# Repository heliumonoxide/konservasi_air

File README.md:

# Water Quality Monitoring Device

## Introduction
This project is **a Water Quality Monitoring System** supported by both a web interface and an OLED display. The device utilizes the SPIFFS (SPI Flash File System) feature of the ESP32 microcontroller to deploy a native web application (HTML, CSS, JavaScript) over a wide-area local network. The system directly links the web interface to real-time data received by the ESP32, providing users with seamless access to water quality metrics. 
 
### Concerns
The Drinking Fountain is essential for students at the Faculty of Engineering, Universitas Indonesia, providing water and reducing plastic use. However, concerns about water quality have led 60% of students to still purchase bottled water. A survey revealed that 90% of respondents believe the water quality in certain buildings is poor, particularly due to its taste. Addressing these concerns is crucial to encouraging students to trust and use the water fountains.

### Usage
1. The device measures all test parameters on drinking water samples.
2. It displays results in a human-readable format via an OLED screen.
3. The device sends water test data to a designed webpage.
4. Its microcontroller deploys a server-based webpage accessible to anyone on the UI Wi-Fi, providing water fountain quality information.

## PCB Design
PCB made using Altium and printed using PCB printing machine.
\

> Here are the made PCB picture
> \
> 
## Hardware Design

## Requirements Software
For installation, within Arduino IDE, the following libraries needs to be installed under Sketch -> Include Library -> Manage Libraries:
* ArduinoJson by Benoit Blanchon
* WebSockets by Markus Sattler
* WiFi 

The following to libraries need to be downloaded, unpacked and copied to the "Arduino" folder (Required for ESPAsyncWebServer)
- https://github.com/me-no-dev/ESPAsyncWebServerWater
- https://github.com/me-no-dev/AsyncTCP

Required to make SPIFFS.h work:
https://github.com/me-no-dev/arduino-esp32fs-plugin/releases/

### How to Install Packages Manually
- Click on the link provided in each package
- Download zip file of the packages through the 'code' dropdown
- Unzip/extract the downloaded file
- Put the packages folder in to libraries folder in Arduino Folder (usually in C:/Users/Documents/Arduino)

### How to Install Tools Manually
- Click on the link provided in each package
- Download zip file of the tools in the asset section of the page
- Unzip/extract the downloaded file
- Put the asset folder into tools folder in Arduino Folder (usually in C:/Users/Documents/Arduino)
- After putting asset folder into tools folder, restart the Arduino IDE
- Check if in the dropdown section of Tools there is ESP32 Sketch Data Upload
- [X] if there is, then you are set to go

## Code Pre-configuration
In the ino. files in this section,
```
// SSID and password of Wifi connection:
const char* ssid = "[Your Wifi Name]";
const char* password = "[Your Wifi Password]";
```
ssid and password need to be changed according to the router/wifi that is used.

> Before uploading the code, **please upload data sketch first using ESP32 Sketch Data Upload button on tools dropdown section**

## Hardware Requirement
Before making the actual device, there are some items that you need to have:
- Analog pH Sensor kit by DFRobot
- OleD White 0.96 inch I2C IIC 128x64 display module lcd
- Oled Display 0.91 inch 128x32 LCD Screen
- Micro DC step down 4v-24v to 3.3v 5v 3A Buck super mini
- ESP32
- KY-023 Analog Dual Axis XY Joystick
- Calibration Buffer Powder/liquid
- PH Meter Sensor board ph4502C for Arduino
- Robotdyn e 3.3v/5v logic 4A/16A 600V for Arduino - 4A
- PTC Thermostat
- Heatsink
- Hi-Link HLK-5M05
- Modul 16bit I2C ADS1115
- Jumper set
- NTC Thermistor
- TDS Sensor
- Turbidity Sensor
- Servo

> Before using all the sensor, please configurate and calibrate first.
## Created by
Bryan Indarto, Aldy Raja, Theonaldo, dan Reza Febrian

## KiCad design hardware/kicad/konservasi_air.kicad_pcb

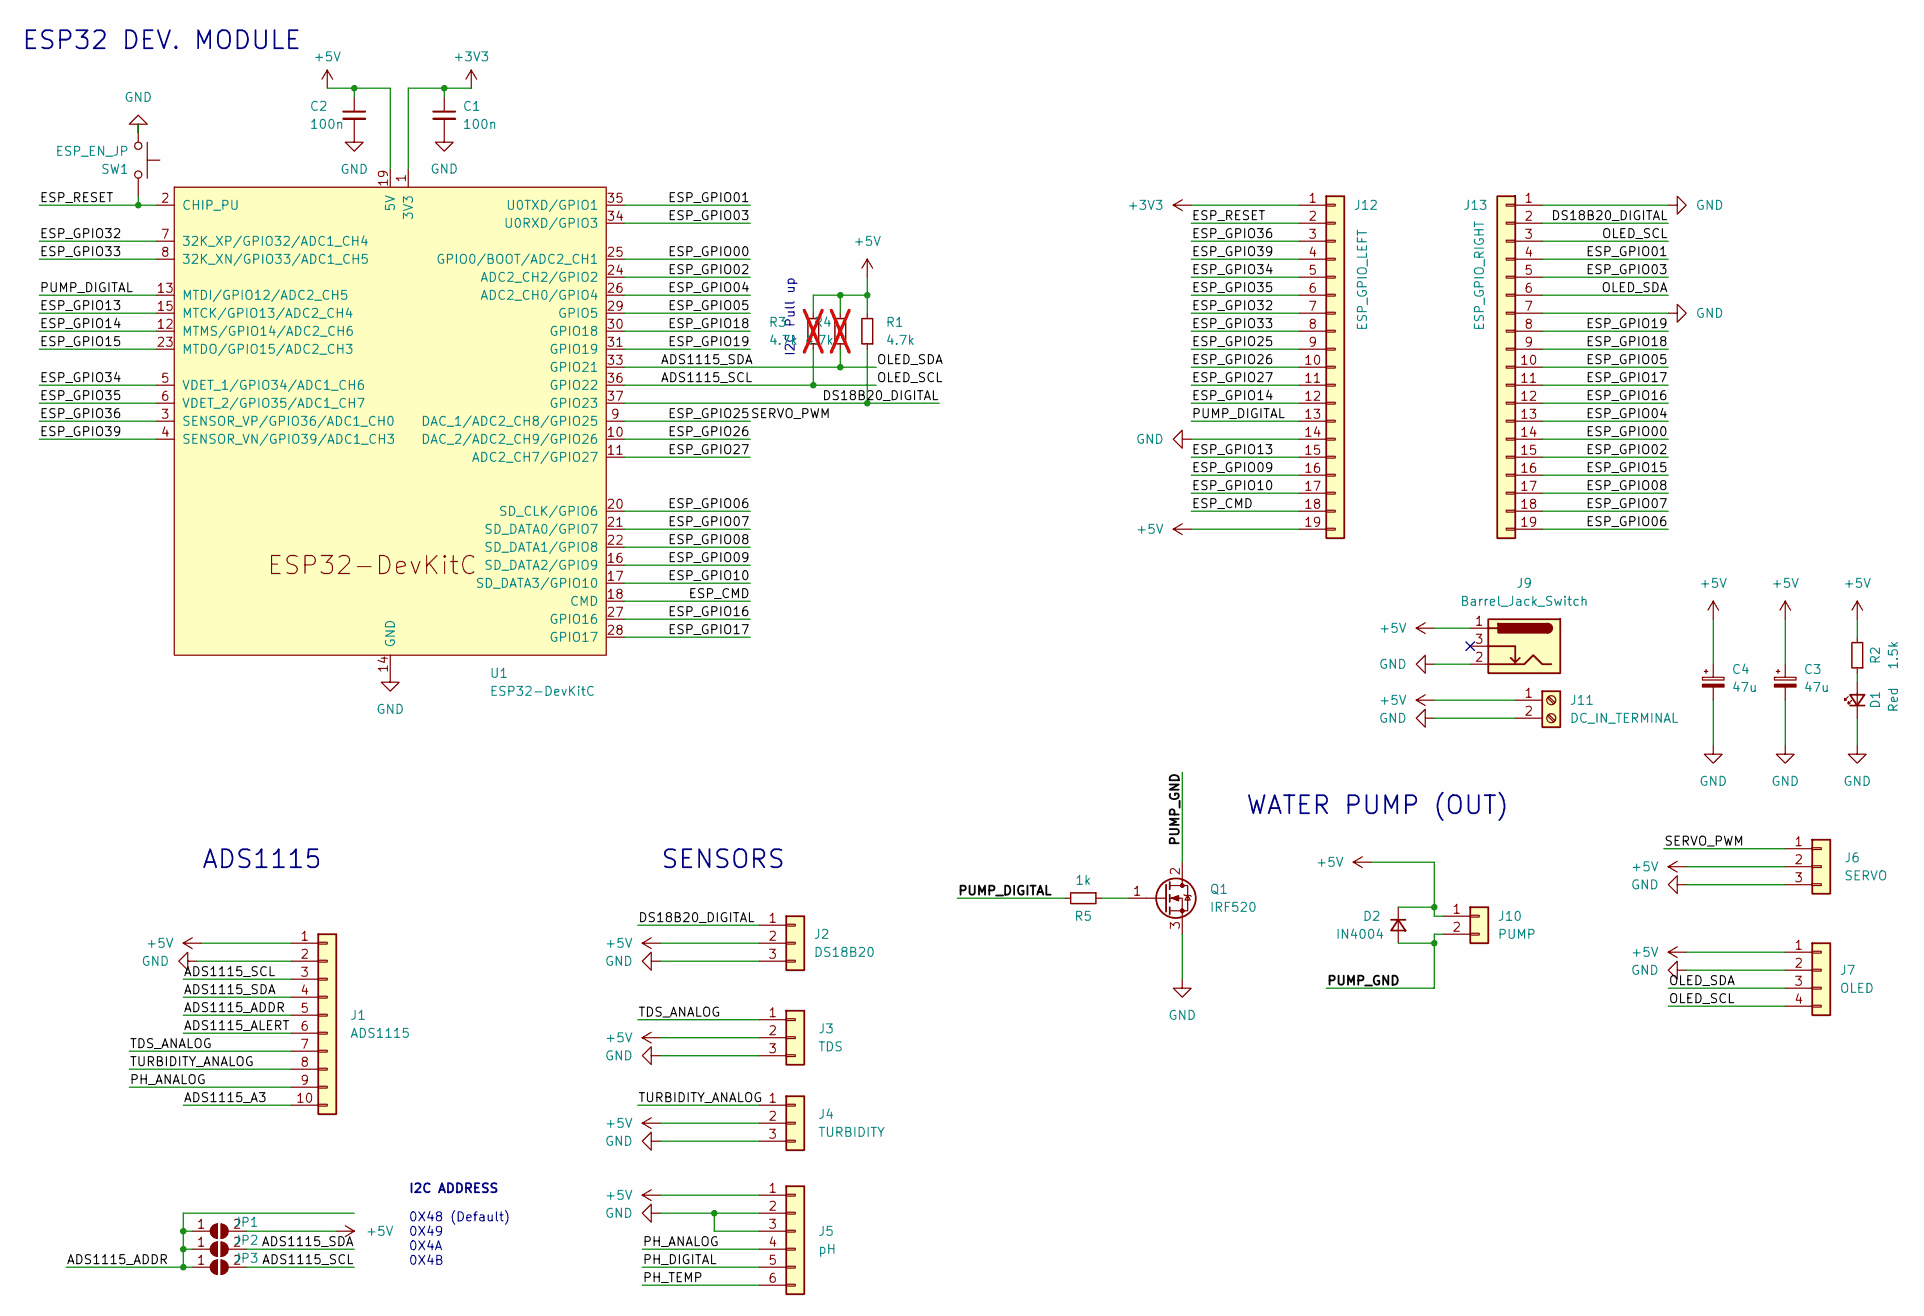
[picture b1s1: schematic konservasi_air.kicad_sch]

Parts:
C1, C2: 100n; C_Disc_D5.0mm_W2.5mm_P5.00mm
C3, C4: 47u; C_Radial_D5.0mm_H11.0mm_P2.00mm
D1: Red; LED_D3.0mm
D2: IN4004; D_DO-34_SOD68_P7.62mm_Horizontal
J1: ADS1115; PinSocket_1x10_P2.54mm_Vertical
J2: DS18B20; Molex_SL_171971-0003_1x03_P2.54mm_Vertical
J3: TDS; Molex_SL_171971-0003_1x03_P2.54mm_Vertical
J4: TURBIDITY; Molex_SL_171971-0003_1x03_P2.54mm_Vertical
J5: pH; Molex_SL_171971-0006_1x06_P2.54mm_Vertical
J6: SERVO; Molex_SL_171971-0003_1x03_P2.54mm_Vertical
J7: OLED; Molex_SL_171971-0004_1x04_P2.54mm_Vertical
J9: Barrel_Jack_Switch; BarrelJack_Horizontal
J10: PUMP; Molex_SL_171971-0002_1x02_P2.54mm_Vertical
J11: DC_IN_TERMINAL; TerminalBlock_Phoenix_MPT-0,5-2-2.54_1x02_P2.54mm_Horizontal
J12: ESP_GPIO_LEFT; PinHeader_1x19_P2.54mm_Vertical
J13: ESP_GPIO_RIGHT; PinHeader_1x19_P2.54mm_Vertical
JP1: ADS1115_ADDR_5V; SolderJumper-2_P1.3mm_Open_RoundedPad1.0x1.5mm
JP2: ADS1115_ADDR_SDA; SolderJumper-2_P1.3mm_Open_RoundedPad1.0x1.5mm
JP3: ADS1115_ADDR_SCL; SolderJumper-2_P1.3mm_Open_RoundedPad1.0x1.5mm
Q1: IRF520; TO-220-3_Vertical
R1: 4.7k; R_Axial_DIN0204_L3.6mm_D1.6mm_P7.62mm_Horizontal
R2: 1.5k; R_Axial_DIN0204_L3.6mm_D1.6mm_P7.62mm_Horizontal
R3, R4: 4.7k; R_Axial_DIN0204_L3.6mm_D1.6mm_P7.62mm_Horizontal; not fitted
R5: 1k; R_Axial_DIN0204_L3.6mm_D1.6mm_P7.62mm_Horizontal
SW1: ESP_EN_JP; Molex_SL_171971-0002_1x02_P2.54mm_Vertical
U1: ESP32-DevKitC

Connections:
+3V3: C1.1, J12.1, U1.1 (3V3)
+5V: C2.1, C3.1, C4.1, D2.1 (K), J1.1, J2.2, J3.2, J4.2, J5.1, J6.2, J7.1, J9.1, J10.1, J11.1, J12.19, JP1.2 (B), R1.2, R2.2, R3.2, R4.2, U1.19 (5V)
/ADS1115_A3: J1.10
/ADS1115_ADDR: J1.5, JP1.1 (A), JP2.1 (A), JP3.1 (A)
/ADS1115_ALERT: J1.6
/ADS1115_SCL: J1.3, J7.4, J13.3, JP3.2 (B), R3.1, U1.36 (GPIO22)
/ADS1115_SDA: J1.4, J7.3, J13.6, JP2.2 (B), R4.1, U1.33 (GPIO21)
/DS18B20_DIGITAL: J2.1, J13.2, R1.1, U1.37 (GPIO23)
/ESP_CMD: J12.18, U1.18 (CMD)
/ESP_GPIO00: J13.14, U1.25 (GPIO0/BOOT/ADC2_CH1)
/ESP_GPIO01: J13.4, U1.35 (U0TXD/GPIO1)
/ESP_GPIO02: J13.15, U1.24 (ADC2_CH2/GPIO2)
/ESP_GPIO03: J13.5, U1.34 (U0RXD/GPIO3)
/ESP_GPIO04: J13.13, U1.26 (ADC2_CH0/GPIO4)
/ESP_GPIO05: J13.10, U1.29 (GPIO5)
/ESP_GPIO06: J13.19, U1.20 (SD_CLK/GPIO6)
/ESP_GPIO07: J13.18, U1.21 (SD_DATA0/GPIO7)
/ESP_GPIO08: J13.17, U1.22 (SD_DATA1/GPIO8)
/ESP_GPIO09: J12.16, U1.16 (SD_DATA2/GPIO9)
/ESP_GPIO10: J12.17, U1.17 (SD_DATA3/GPIO10)
/ESP_GPIO13: J12.15, U1.15 (MTCK/GPIO13/ADC2_CH4)
/ESP_GPIO14: J12.12, U1.12 (MTMS/GPIO14/ADC2_CH6)
/ESP_GPIO15: J13.16, U1.23 (MTDO/GPIO15/ADC2_CH3)
/ESP_GPIO16: J13.12, U1.27 (GPIO16)
/ESP_GPIO17: J13.11, U1.28 (GPIO17)
/ESP_GPIO18: J13.9, U1.30 (GPIO18)
/ESP_GPIO19: J13.8, U1.31 (GPIO19)
/ESP_GPIO25: J6.1, J12.9, U1.9 (DAC_1/ADC2_CH8/GPIO25)
/ESP_GPIO26: J12.10, U1.10 (DAC_2/ADC2_CH9/GPIO26)
/ESP_GPIO27: J12.11, U1.11 (ADC2_CH7/GPIO27)
/ESP_GPIO32: J12.7, U1.7 (32K_XP/GPIO32/ADC1_CH4)
/ESP_GPIO33: J12.8, U1.8 (32K_XN/GPIO33/ADC1_CH5)
/ESP_GPIO34: J12.5, U1.5 (VDET_1/GPIO34/ADC1_CH6)
/ESP_GPIO35: J12.6, U1.6 (VDET_2/GPIO35/ADC1_CH7)
/ESP_GPIO36: J12.3, U1.3 (SENSOR_VP/GPIO36/ADC1_CH0)
/ESP_GPIO39: J12.4, U1.4 (SENSOR_VN/GPIO39/ADC1_CH3)
/ESP_RESET: J12.2, SW1.2, U1.2 (CHIP_PU)
/PH_ANALOG: J1.9, J5.4
/PH_DIGITAL: J5.5
/PH_TEMP: J5.6
/PUMP_DIGITAL: J12.13, R5.2, U1.13 (MTDI/GPIO12/ADC2_CH5)
/PUMP_GND: D2.2 (A), J10.2, Q1.2 (D)
/TDS_ANALOG: J1.7, J3.1
/TURBIDITY_ANALOG: J1.8, J4.1
GND: C1.2, C2.2, C3.2, C4.2, D1.1 (K), J1.2, J2.3, J3.3, J4.3, J5.2, J5.3, J6.3, J7.2, J9.2, J11.2, J12.14, J13.1, J13.7, Q1.3 (S), SW1.1, U1.14 (GND), U1.32 (GND), U1.38 (GND)
unnamed: D1.2 (A), R2.1
unnamed: Q1.1 (G), R5.1

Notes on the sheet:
ESP32 DEV. MODULE
ADS1115
I2C Pull up
WATER PUMP (OUT)
I2C ADDRESS
0X48 (Default) 0X49 0X4A 0X4B
SENSORS

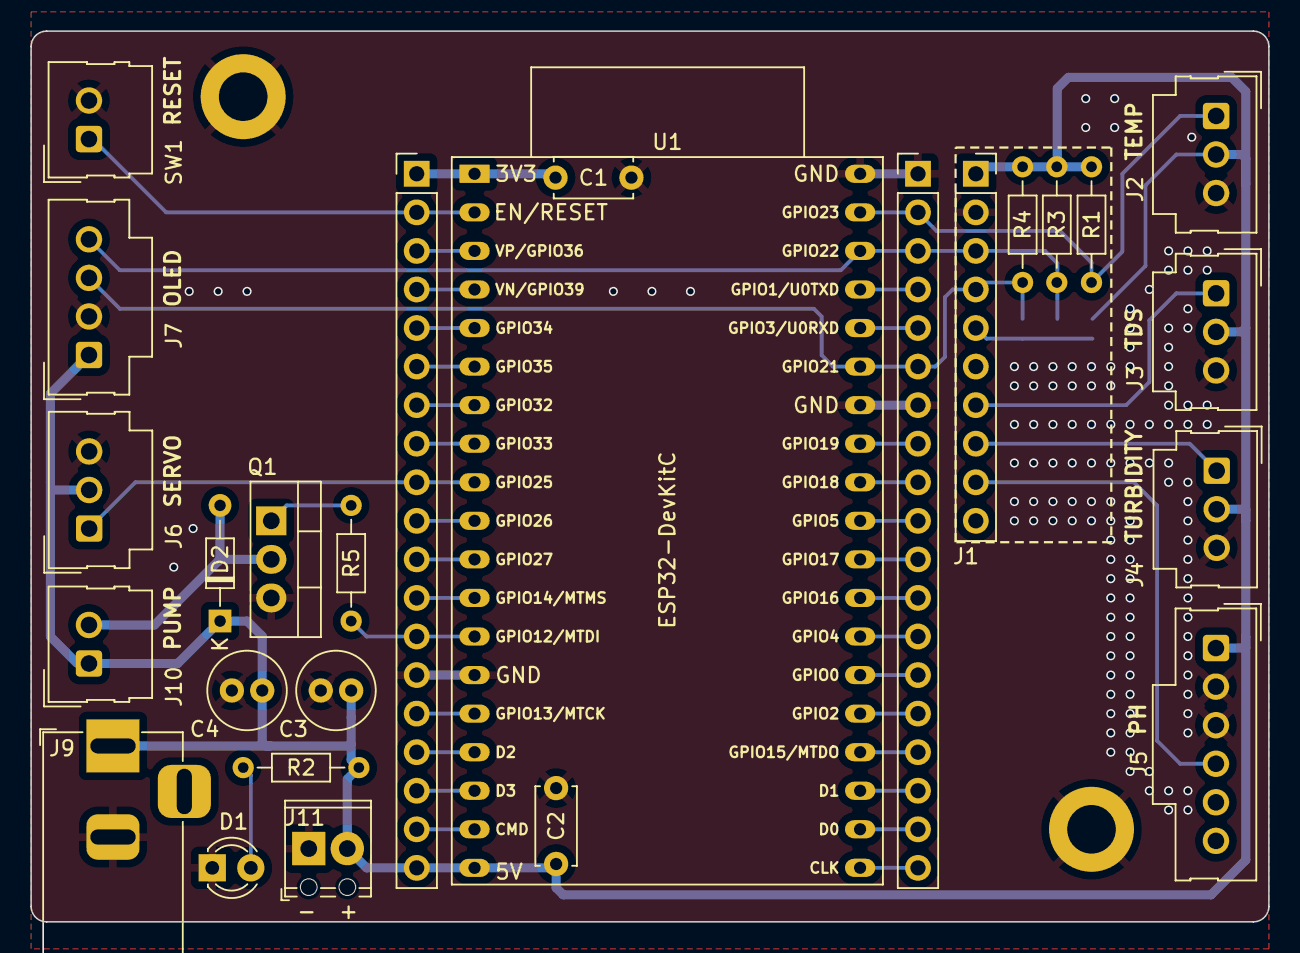
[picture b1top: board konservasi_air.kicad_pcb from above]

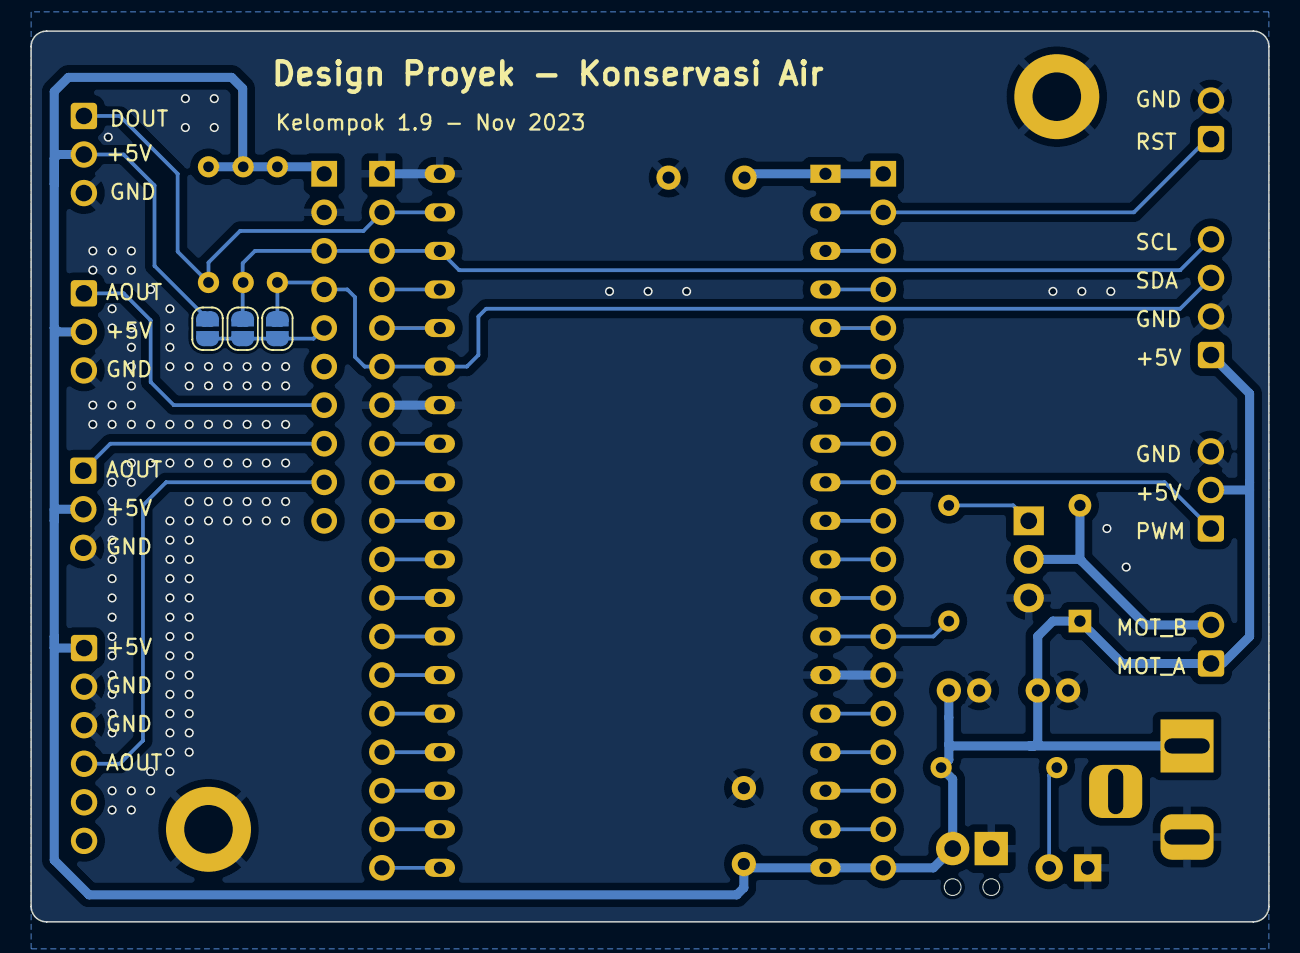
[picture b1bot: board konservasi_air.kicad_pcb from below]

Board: 2 copper layers, 81.5 x 58.7 mm, 29 parts (3 on the bottom side), 43 nets.

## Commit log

2023-09-16 ino added
2023-09-18 update ino
2023-09-19 Wifi address changed
2023-09-23 Front-end: Navbar and time added
2023-09-23 front-end: page modified
2023-09-23 page more responsive
2023-09-25 update front end: more responsive
2023-09-27 chart bar updated
2023-10-02 added pH tds ntu responsive bar
2023-10-11 Add serial reading for sensor
    reading for sensor 5V
2023-10-11 update Voltage Reference
2023-10-23 Serial Prototyping Modified
2023-10-23 modified
2023-10-30 Serial Prototyping 70% Done
2023-10-31 pH Sensor Modified
2023-11-02 display sensor values on server
2023-11-05 Progress Bar Modified
2023-11-05 Value bar completed
2023-11-05 Major bug fixed
2023-11-07 Minor bug fixed
2023-11-10 Up Kicad Project
2023-11-10 Update Schematics
2023-11-12 PCB Layout Update
2023-11-12 PCB Update
2023-11-13 Done Routing
2023-11-15 Serial Integrated with Webpage
2023-11-17 PCB Modified
2023-11-17 Update PCB
2023-11-19 Fix Pullup for Temp Sensor
2023-11-19 Added Production File (Gerber)
2023-11-21 Backup added
2023-11-22 add ads1115
2023-12-12 final
2023-12-12 update dikit
2024-09-07 Update README.md
    Beautify Readme
2024-09-07 Added functionality to device (#1)
    * final
    * update dikit
    ---------
